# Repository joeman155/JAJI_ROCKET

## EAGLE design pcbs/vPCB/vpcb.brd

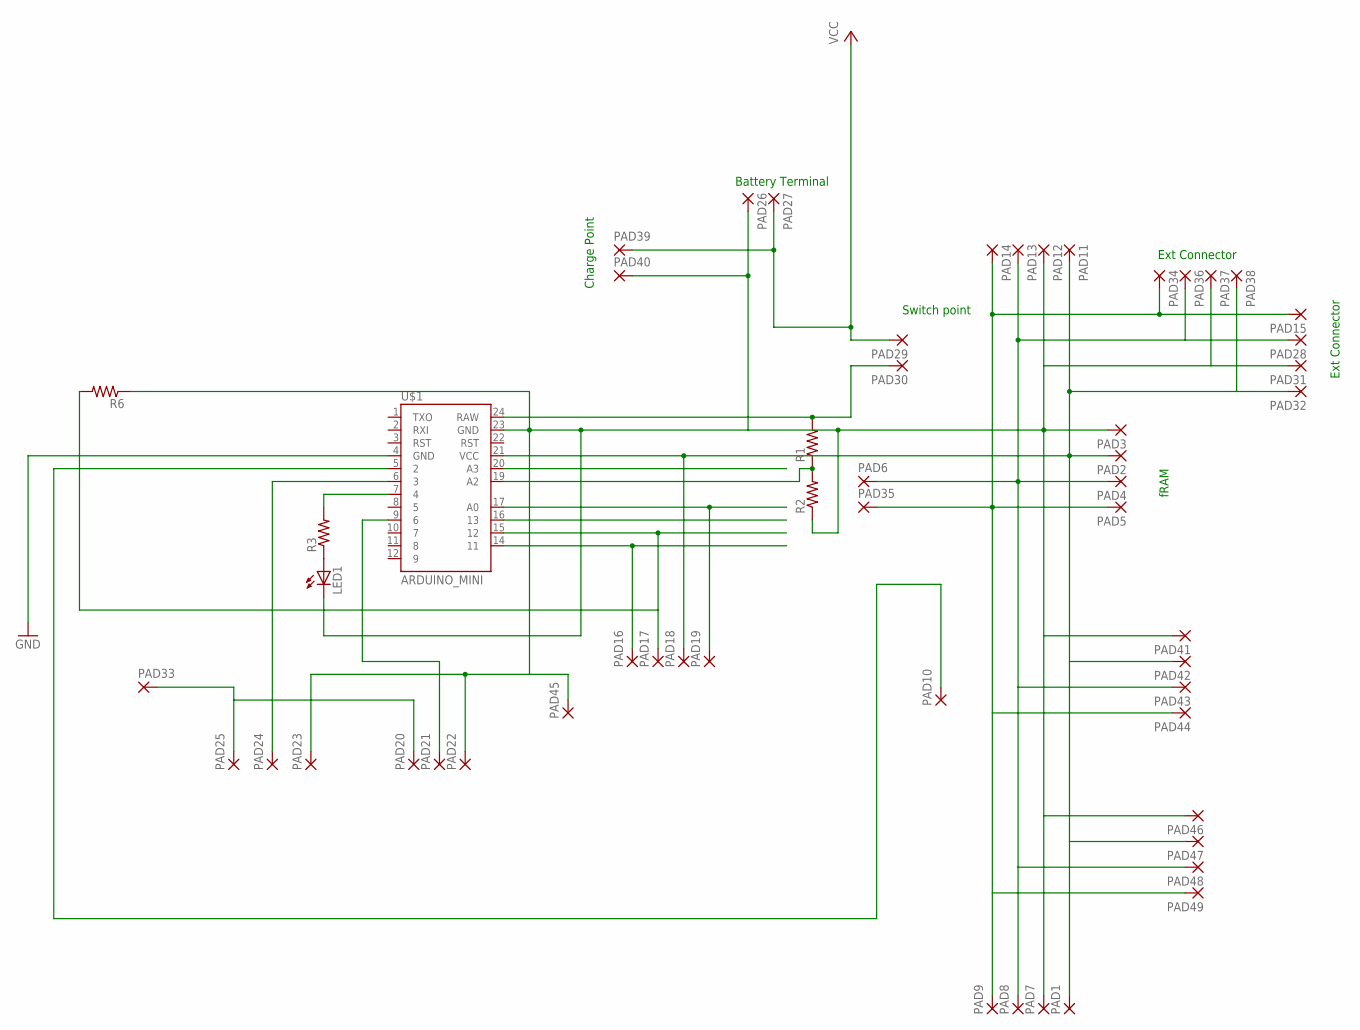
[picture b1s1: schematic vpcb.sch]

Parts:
LED1: LED3MM
PAD1, PAD2, PAD3, PAD4, PAD5, PAD6, PAD7, PAD8, PAD9, PAD10, PAD11, PAD12, PAD13, PAD14, PAD15, PAD16, PAD17, PAD18, PAD19, PAD20, PAD21, PAD22, PAD23, PAD24, PAD25, PAD26, PAD27, PAD28, PAD29, PAD30, PAD31, PAD32, PAD33, PAD34, PAD35, PAD36, PAD37, PAD38, PAD39, PAD40, PAD41, PAD42, PAD43, PAD44, PAD45, PAD46, PAD47, PAD48, PAD49: 2,15/1,0
R1, R2, R3: R-US_0204/7; 0204/7
R6: R-US_0204/5; 0204/5
U$1: ARDUINO_MINI

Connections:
GND: U$1.4 (GND)
unnamed: PAD4.1, PAD6.1, PAD8.1, PAD13.1, PAD28.1, PAD36.1, PAD43.1, PAD48.1
unnamed: PAD5.1, PAD9.1, PAD14.1, PAD15.1, PAD34.1, PAD35.1, PAD44.1, PAD49.1
unnamed: PAD1.1, PAD2.1, PAD11.1, PAD18.1, PAD32.1, PAD38.1, PAD42.1, PAD47.1, U$1.21 (VCC)
unnamed: PAD30.1, R1.2, U$1.24 (RAW)
unnamed: PAD10.1, U$1.5 (2)
unnamed: PAD20.1, PAD25.1, PAD33.1
unnamed: R1.1, R2.2, U$1.19 (A2)
unnamed: LED1.A, R3.1
unnamed: PAD19.1, U$1.17 (A0)
unnamed: R3.2, U$1.7 (4)
unnamed: PAD24.1, U$1.6 (3)
unnamed: PAD21.1, U$1.9 (6)
unnamed: LED1.K (C), PAD3.1, PAD7.1, PAD12.1, PAD22.1, PAD23.1, PAD26.1, PAD31.1, PAD37.1, PAD40.1, PAD41.1, PAD45.1, PAD46.1, R2.1, R6.1, U$1.23 (GND)
unnamed: PAD17.1, R6.2, U$1.15 (12)
unnamed: PAD16.1, U$1.14 (11)
VCC: PAD27.1, PAD29.1, PAD39.1

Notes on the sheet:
Switch point
Charge Point
Ext Connector
fRAM
Battery Terminal

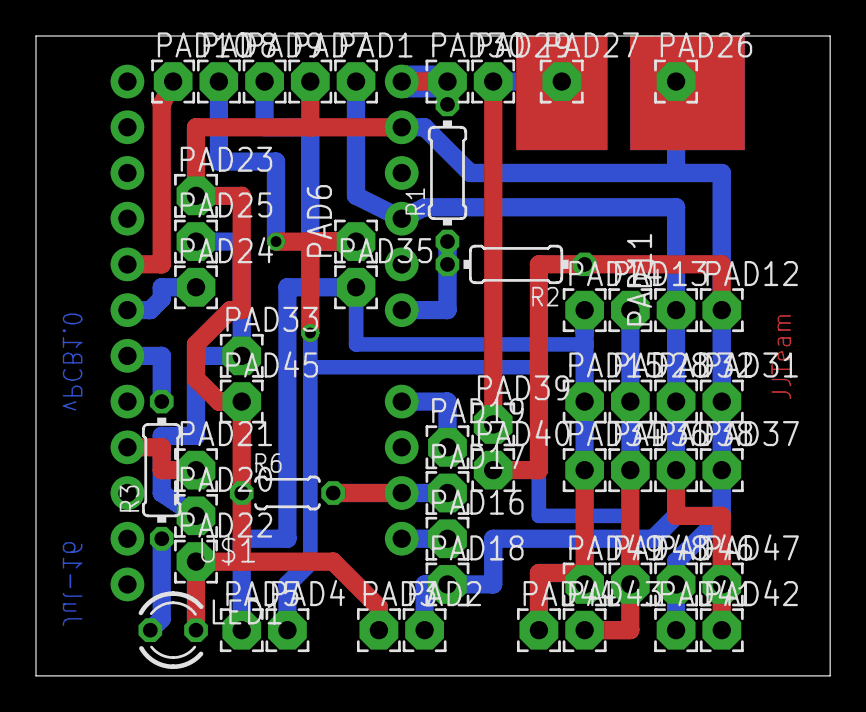
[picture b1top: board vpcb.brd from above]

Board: 2 copper layers, 44.1 x 35.5 mm, 55 parts (0 on the bottom side), 16 nets.

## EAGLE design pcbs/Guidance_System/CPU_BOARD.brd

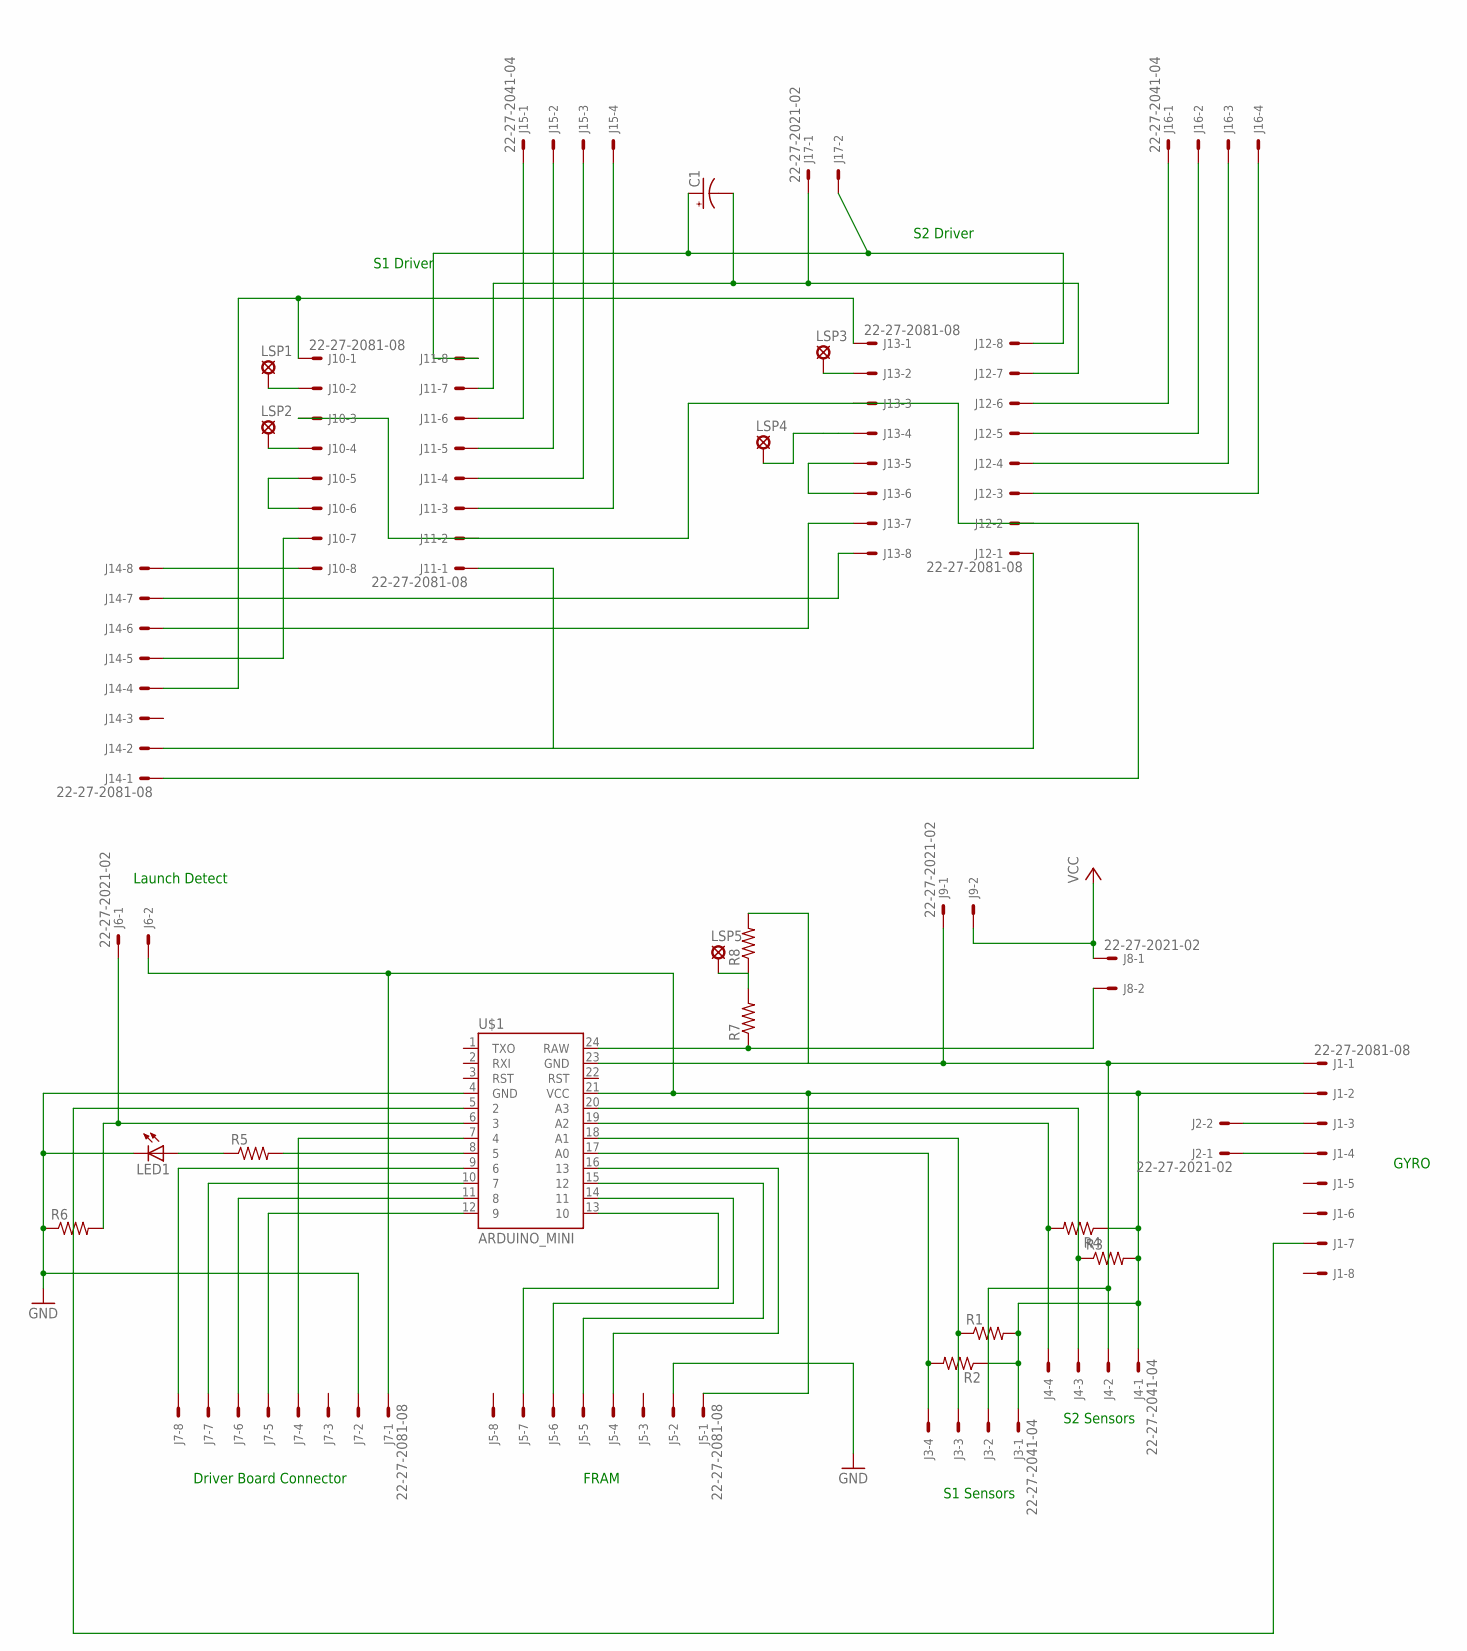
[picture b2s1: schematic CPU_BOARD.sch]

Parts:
C1: CPOL-USE2.5-7; E2,5-7
J1, J5, J7, J10, J11, J12, J13, J14: 22-27-2081-08; 6410-08
J2, J6, J8, J9, J17: 22-27-2021-02; 6410-02
J3, J4, J15, J16: 22-27-2041-04; 6410-04
LED1: LED5MM
LSP1, LSP2, LSP3, LSP4: LSP10
LSP5: LSP11
R1, R2, R3, R4, R5, R6, R7, R8: R-US_0204/5; 0204/5
U$1: ARDUINO_MINI

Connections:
GND: J5.2, J7.2, LED1.K (C), R6.1, U$1.4 (GND)
unnamed: J1.3, J2.2
unnamed: J1.4, J2.1
unnamed: J1.2, J3.1, J4.1, J5.1, J6.2, J7.1, R1.2, R2.1, R3.2, R4.1, U$1.21 (VCC)
unnamed: J10.5, J10.6
unnamed: J8.2, R7.1, U$1.24 (RAW)
unnamed: J1.7, U$1.5 (2)
unnamed: J5.7, U$1.13 (10)
unnamed: J5.6, U$1.14 (11)
unnamed: J4.3, R3.1, U$1.20 (A3)
unnamed: J4.4, R4.2, U$1.19 (A2)
unnamed: J3.3, R1.1, U$1.18 (A1)
unnamed: J3.4, R2.2, U$1.17 (A0)
unnamed: J5.5, U$1.15 (12)
unnamed: J5.4, U$1.16 (13)
unnamed: R5.2, U$1.8 (5)
unnamed: LED1.A, R5.1
unnamed: J6.1, R6.2, U$1.6 (3)
unnamed: J7.8, U$1.9 (6)
unnamed: J13.5, J13.6
unnamed: J7.7, U$1.10 (7)
unnamed: J7.6, U$1.11 (8)
unnamed: J7.5, U$1.12 (9)
unnamed: J7.4, U$1.7 (4)
unnamed: J1.1, J3.2, J4.2, J9.1, R8.2, U$1.23 (GND)
unnamed: J10.4, LSP2.MP
unnamed: J10.8, J14.8
unnamed: J10.7, J14.5
unnamed: J13.7, J14.6
unnamed: J13.8, J14.7
unnamed: J10.2, LSP1.MP
unnamed: C1.+, J11.8, J12.8, J17.2
unnamed: J10.3, J11.2, J12.2, J13.3, J14.1
unnamed: J11.1, J12.1, J14.2
unnamed: C1.-, J11.7, J12.7, J17.1
unnamed: J10.1, J13.1, J14.4
unnamed: J13.4, LSP4.MP
unnamed: J11.6, J15.1
unnamed: J11.5, J15.2
unnamed: J11.4, J15.3
unnamed: J11.3, J15.4
unnamed: J12.6, J16.1
unnamed: J12.5, J16.2
unnamed: J12.4, J16.3
unnamed: J12.3, J16.4
unnamed: J13.2, LSP3.MP
unnamed: LSP5.MP, R7.2, R8.1
VCC: J8.1, J9.2

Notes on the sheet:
FRAM
S1 Sensors
S2 Sensors
GYRO
Launch Detect
Driver Board Connector
S1 Driver
S2 Driver

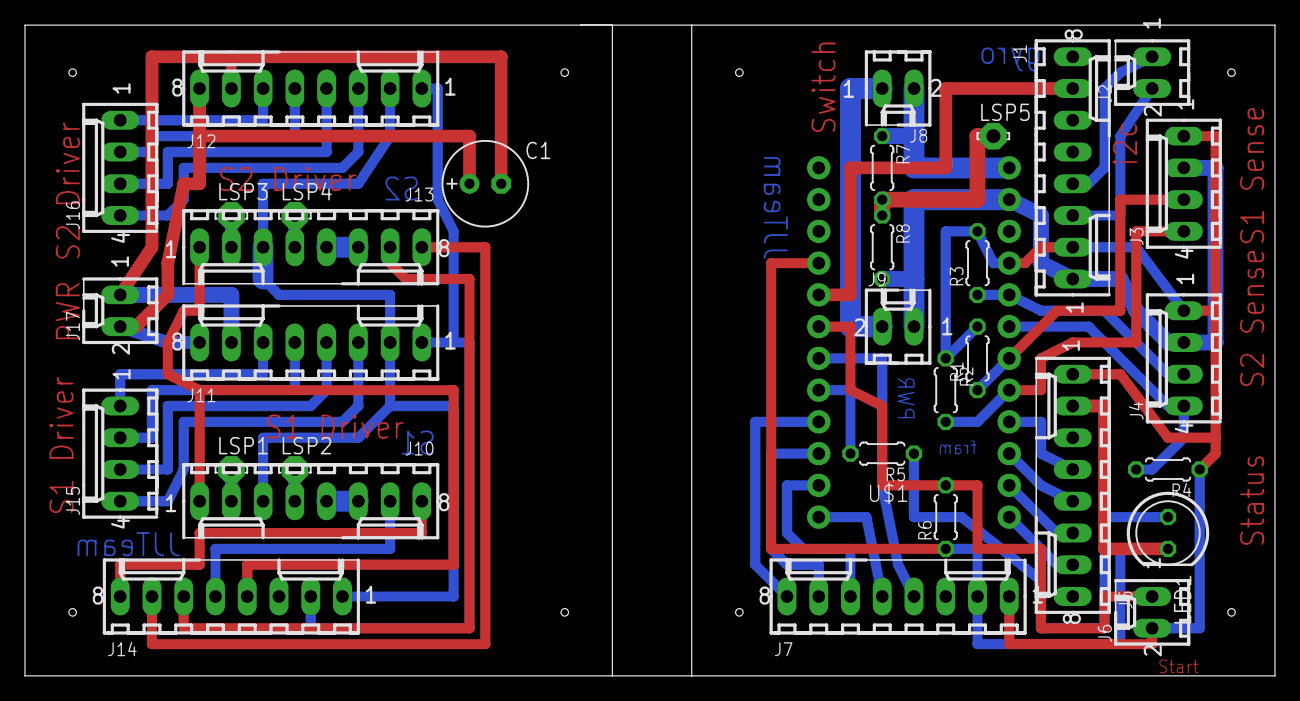
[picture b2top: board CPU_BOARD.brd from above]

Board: 2 copper layers, 100.0 x 52.1 mm, 33 parts (0 on the bottom side), 48 nets.

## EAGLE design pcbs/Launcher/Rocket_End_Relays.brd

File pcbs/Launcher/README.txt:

These files are PCB designs of circuits to launch rockets. These are
shields that will fit on a Freetronics EtherMega

Rocket_End - Signifies PCBS that reside in electronics at end where 
             rocket is.

Operator_End - (No files as of yet)

The second part indicates the main component on them.
- Relays  - Means relays to perform launch sequence 
 [There is also facility for camera and RFD900 module]

- Sensors - A pile of sensors that might be useful
 [Sensors/devices include CopernicusGPS, RTC, IMU, Air pressure measurement]

As you can appreciate for normal launch sequence, only the 'Relays' shield is
required. However, for a Rockoon, at will be advantegous to have a 'Sensors'
shield installed as well to help collect other information (GPS, IMU, 
air pressure, temp, etc)

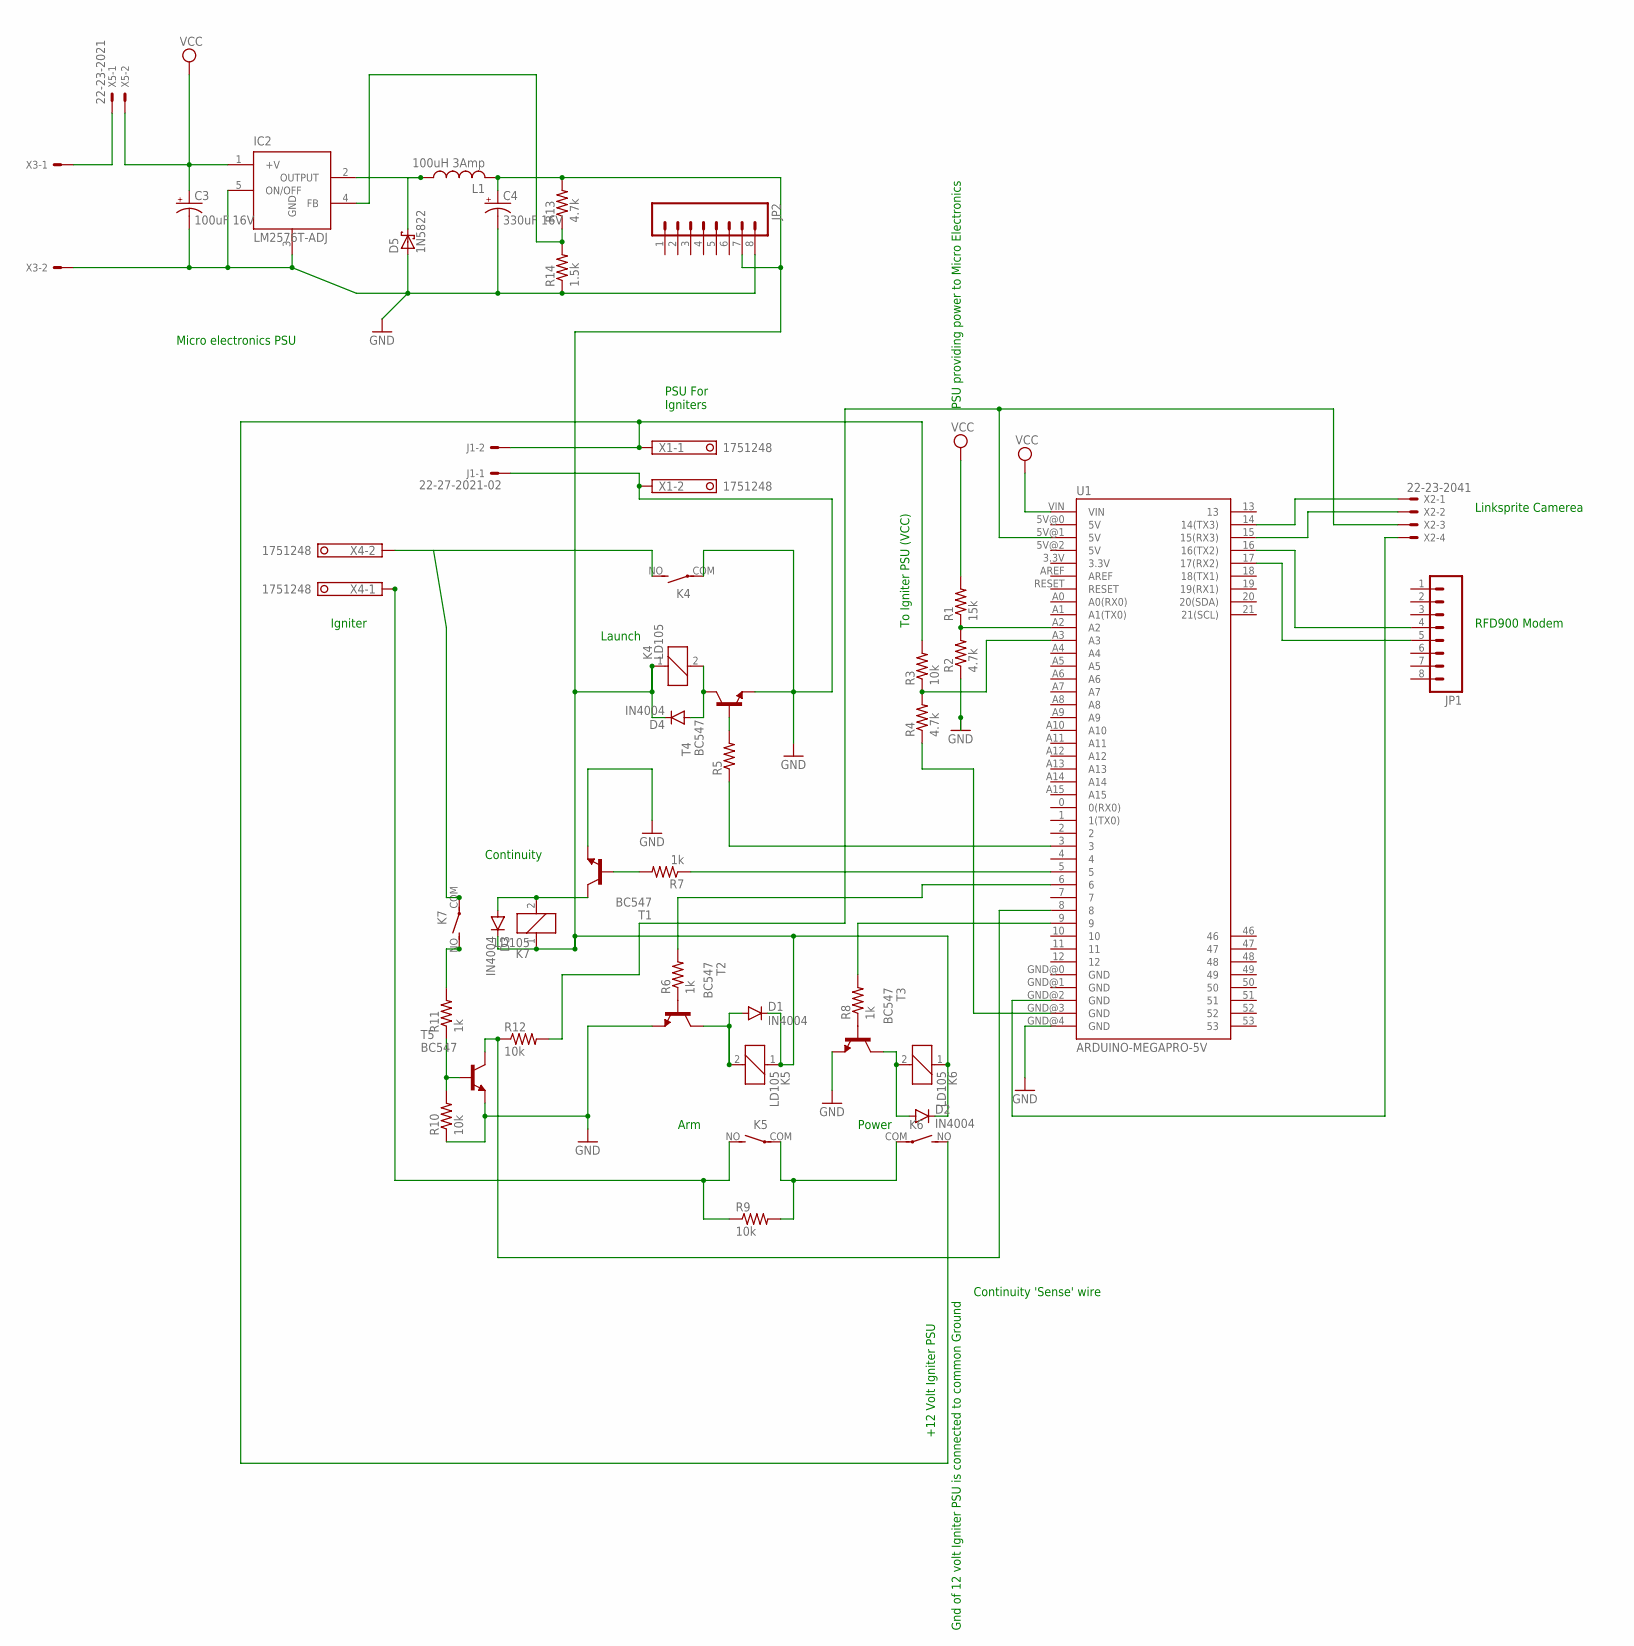
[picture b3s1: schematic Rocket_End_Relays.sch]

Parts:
C3: 100uF 16V; E2-4
C4: 330uF 16V; E2-4
D1, D2, D3, D4: IN4004; DIODE-1N4148
D5: 1N5822; C4111-15
IC2: LM2576T-ADJ; TO220-5
J1: 22-27-2021-02; 6410-02
JP1, JP2: M08; 1X08_ROUND
K4, K5, K6, K7: LD105; LD
L1: 100uH 3Amp; TJ4-U1
R1: 15k; 0204/7
R2, R4: 4.7k; 0204/7
R3, R9, R12: 10k; 0204/7
R5: R-US_0204/7; 0204/7
R6, R7, R8: 1k; 0204/7
R10: 10k; 0207/7
R11: 1k; 0207/12
R13: 4.7k; 0204V
R14: 1.5k; 0207/7
T1, T2, T3, T4, T5: BC547; TO92
U1: ARDUINO-MEGAPRO-5V; ARDUINO_MEGA-PRO-5V
X1, X4: 1751248
X2: 22-23-2041
X3, X5: 22-23-2021

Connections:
unnamed: JP1.4, U1.16 (16(TX2))
unnamed: JP1.5, U1.17 (17(RX2))
unnamed: R3.1, R4.2, U1.A3
unnamed: R7.1, U1.5
unnamed: C4.+, D1.C, D2.C, D3.C, D4.C, JP2.7, K4.1, K5.1, K6.1, K7.1, L1.2, R13.2
unnamed: U1.14 (14(TX3)), X2.1
unnamed: R1.1, R2.2, U1.A2
unnamed: R5.1, U1.3
unnamed: R6.2, U1.6
unnamed: R6.1, T2.2 (B)
unnamed: R8.1, T3.2 (B)
unnamed: R5.2, T4.2 (B)
unnamed: R7.2, T1.2 (B)
unnamed: R8.2, U1.9
unnamed: K4.NO (S), K7.COM, X4.2
unnamed: U1.GND@2 (GND), X2.4
unnamed: K5.NO (S), R9.1, X4.1
unnamed: X3.1, X5.1
unnamed: D4.A, K4.2, T4.3 (C)
unnamed: D3.A, K7.2, T1.3 (C)
unnamed: D2.A, K6.2, T3.3 (C)
unnamed: D1.A, K5.2, T2.3 (C)
unnamed: R12.2, U1.5V@1 (5V), X2.3
unnamed: R4.1, U1.GND@3 (GND)
unnamed: R12.1, T5.3 (C), U1.8
unnamed: U1.15 (15(RX3)), X2.2
unnamed: K5.COM, K6.COM, R9.2
unnamed: J1.2, K6.NO (S), R3.2, X1.1
unnamed: K7.NO (S), R11.2
unnamed: R10.2, R11.1, T5.2 (B)
unnamed: C3.-, C4.-, D5.A, IC2.3 (GND), IC2.5 (ON/OFF), J1.1, JP2.8, K4.COM, R2.1, R10.1, R14.1, T1.1 (E), T2.1 (E), T3.1 (E), T4.1 (E), T5.1 (E), U1.GND@4 (GND), X1.2, X3.2
unnamed: D5.C, IC2.2 (OUTPUT), L1.1
unnamed: IC2.4 (FB), R13.1, R14.2
VCC: C3.+, IC2.1 (+V), R1.2, U1.VIN, X5.2

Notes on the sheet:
Linksprite Camerea
RFD900 Modem
To Igniter PSU (VCC)
Launch
Power
Arm
Continuity
Continuity 'Sense' wire
Igniter
+12 Volt Igniter PSU
Gnd of 12 volt Igniter PSU is connected to common Ground
PSU providing power to Micro Electronics
PSU For Igniters
Micro electronics PSU

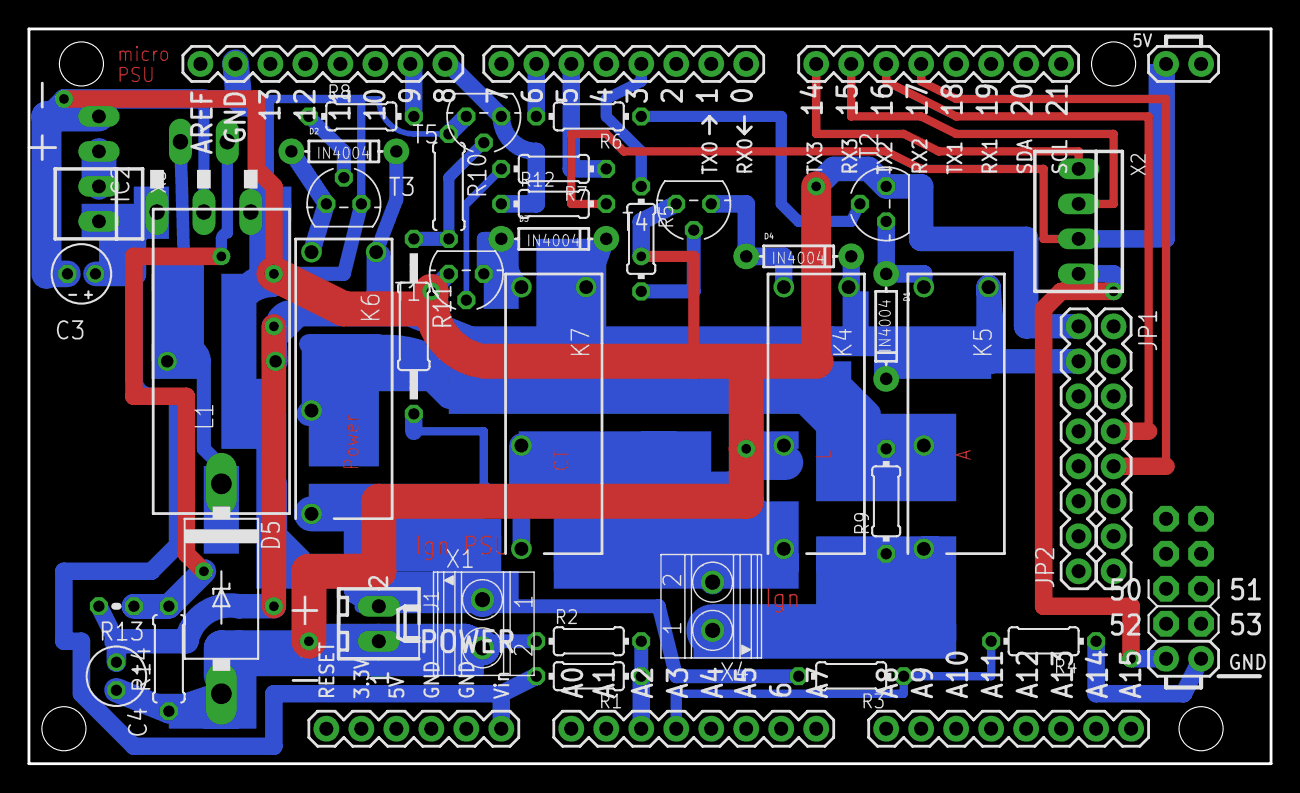
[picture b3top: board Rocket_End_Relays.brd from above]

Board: 2 copper layers, 90.2 x 53.3 mm, 41 parts (1 on the bottom side), 34 nets.

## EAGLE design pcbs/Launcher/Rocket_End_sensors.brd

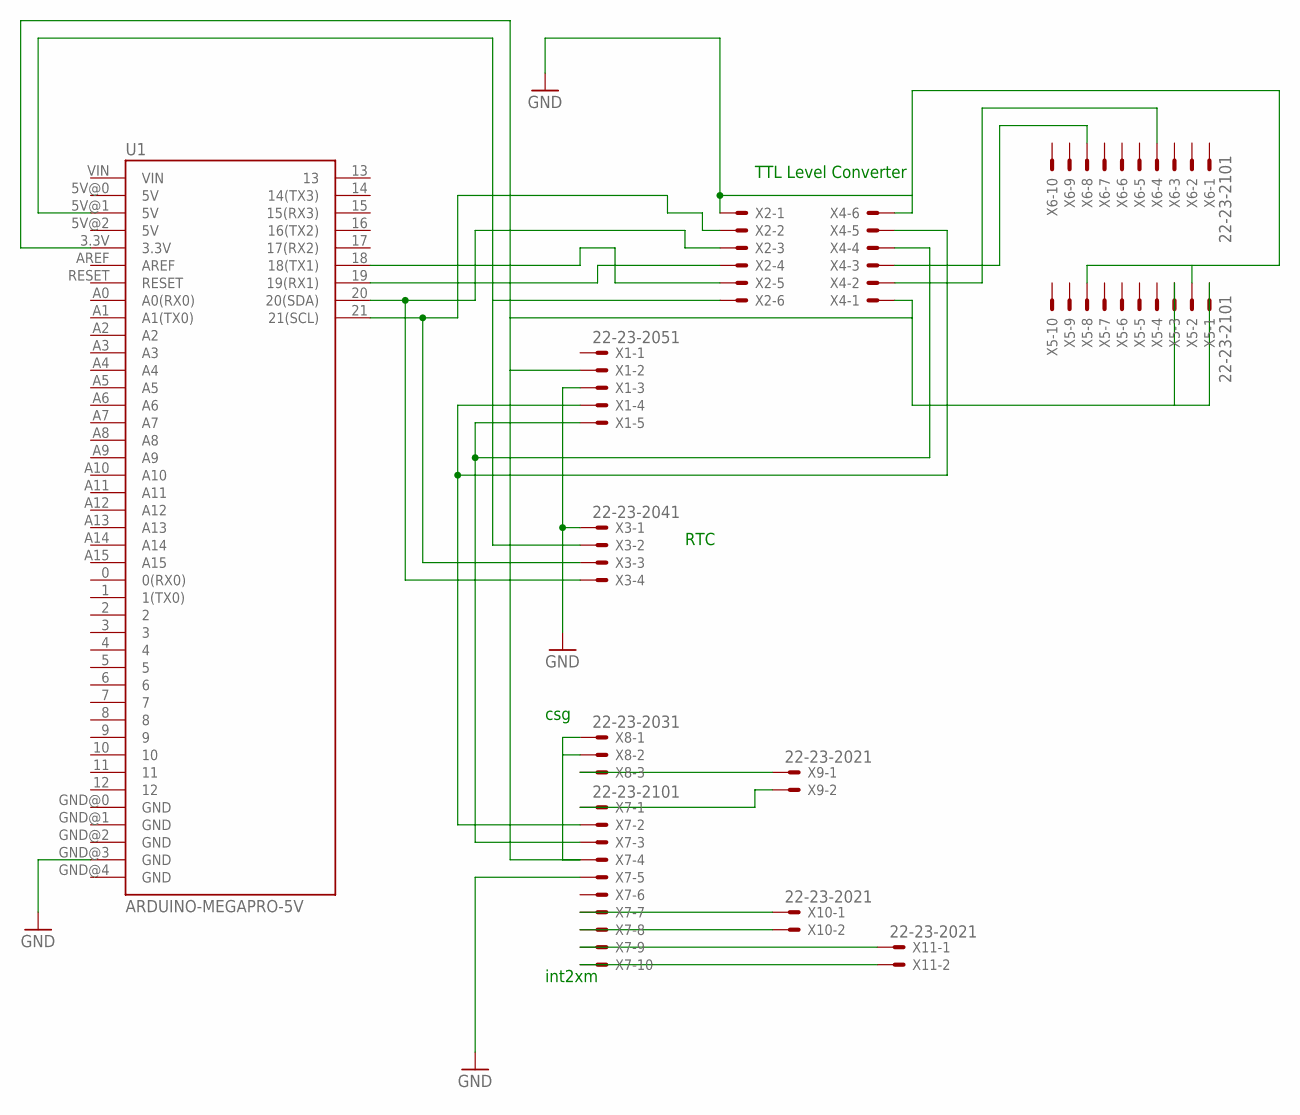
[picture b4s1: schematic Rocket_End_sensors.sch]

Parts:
U1: ARDUINO-MEGAPRO-5V; ARDUINO_MEGA-PRO-5V
X1: 22-23-2051
X2, X4: 22-23-2061
X3: 22-23-2041
X5, X6, X7: 22-23-2101
X8: 22-23-2031
X9, X10, X11: 22-23-2021

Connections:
GND: U1.GND@3 (GND), X1.3, X2.1, X3.1, X4.6, X5.2, X5.8, X7.5
unnamed: U1.19 (19(RX1)), X2.4
unnamed: U1.21 (21(SCL)), X2.2, X3.3
unnamed: U1.18 (18(TX1)), X2.5
unnamed: U1.3.3V, X1.2, X4.1, X5.1, X5.3, X7.4, X8.1, X8.2
unnamed: U1.20 (20(SDA)), X2.3, X3.4
unnamed: X4.3, X6.8
unnamed: X8.3, X9.1
unnamed: X4.2, X6.4
unnamed: X7.1, X9.2
unnamed: X7.7, X10.1
unnamed: X7.8, X10.2
unnamed: X7.9, X11.1
unnamed: X7.10, X11.2
unnamed: X1.5, X4.4, X7.3
unnamed: X1.4, X4.5, X7.2
unnamed: U1.5V@1 (5V), X2.6, X3.2

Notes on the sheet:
RTC
TTL Level Converter
int2xm
csg

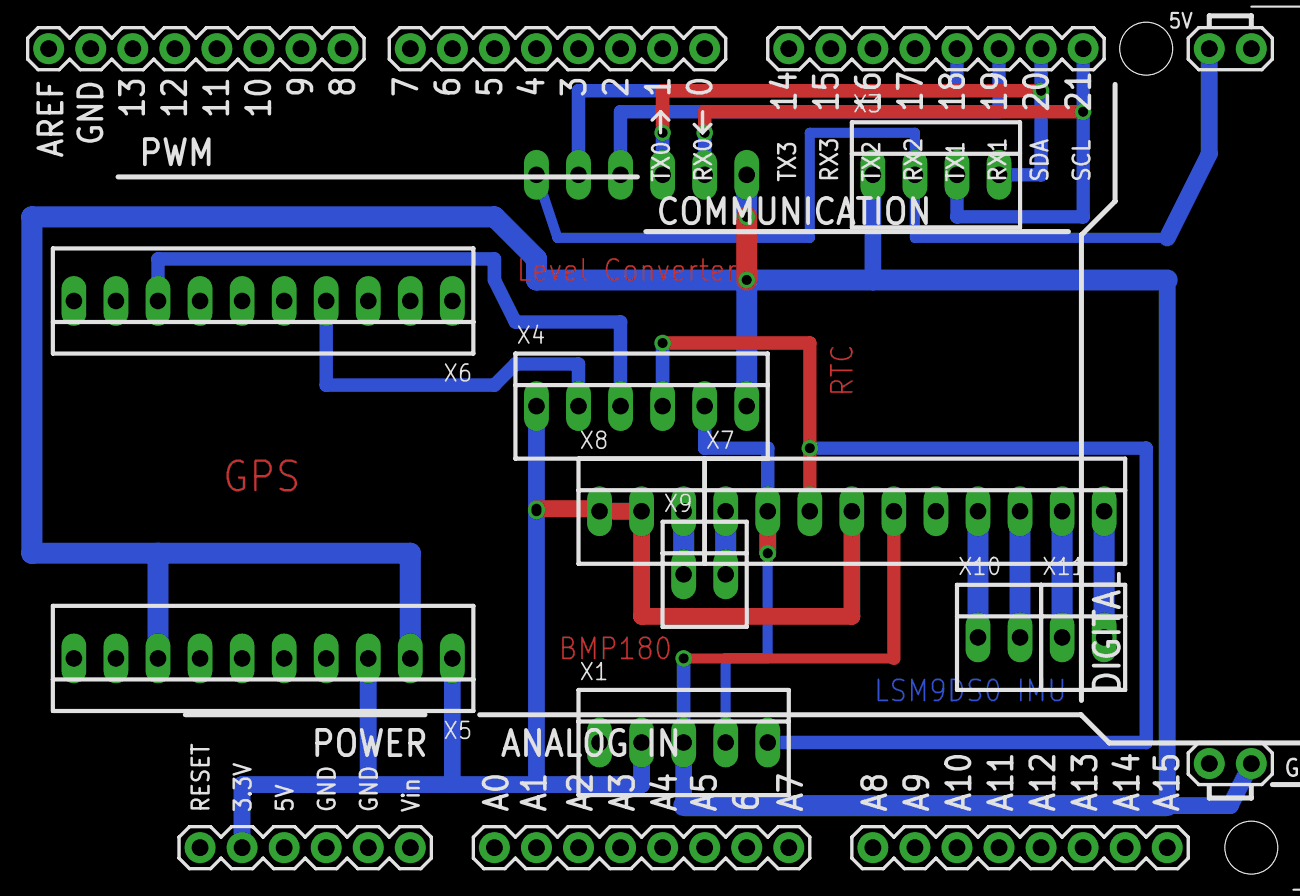
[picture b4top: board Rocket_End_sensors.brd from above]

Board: 2 copper layers, 12 parts (1 on the bottom side), 17 nets.

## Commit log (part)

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2015-07-26 * Add routine to see if pending requests (after latest known status)
2015-07-27 * WOrk on status codeing.
2015-07-27 * Refining way status js is being done.
2015-07-27 * Default photos status
2015-07-28 * Formatting of code * pausing of Hab page added. (reload_paused)
2015-07-28 * Sorted serious issue wit hmore launch_console.php being requested when flipping between pages. restricted to just ONE interval job.
2015-08-03 * Correcting the right-angle connector tracks for a RFD900p module connected logo up. Also made sure it was 10mm from the edge of the pdb * Put in correct 2 pin screw terminal blocks with pitch of 3.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
2015-08-09 * Widened some tracks * Put 2 x 2-pin connector for 7.4 PSU and Switch.
2015-08-10 * Moving across pins, so we don't use pin 4. Pin 4 is used by SDCARD CS.
2015-08-12 * A bit more debugging added.
2015-08-12 * Clarification of pins in comments * Changed Launch Pin to pin 3 * Increased Continuity test delays.
2015-08-16 * Updating web scripts to reflect change in measurements recording.
2015-08-17 * Fixing issue with status page...dbh error.
2015-08-22 * Got Basic IMU working at same time as GPS and RTC.
2015-08-24 * Working on IMU code....commenting out other pieces of code.
2015-08-26 Matix for rotation was incorrect. When rotating around the global Z axis, the computed Z accel changed. It shouldn't have. Put in new matrix.
2015-08-29 * Accepted that Dead Reckoning is not going to work and will implement code so we can atleast monitor its orientation which will still be extremely helpful.
2015-09-03 * More updates.
2015-09-03 * Fix to air pressure measurements.
2015-09-04 * Minor fixes to wording
2015-09-05 * Adding some code to help with Voltage Reader on GroundStation
2015-09-06 * Part way through completing voltage gs code.
2015-09-08 * Reducing some delays * Re-issuing 'M' command if a menu operation is performed. so that further menu requests can be performed.
2015-09-09 * Speed up getting back to menu to do launch and continuity test...by exiting menu after invalidating values * Trying in vain to clear out RX buffers...so that the issue with wrong gotit values is re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
2015-09-09 * Adding in countdown timer.
2015-09-10 * More refinements to tracks, making sure the gaps are sufficiently large.
2015-09-10 * Adding +/- at CPU electronics connector.
2015-09-11 * spacing out some of the components a little * moving the camera serial port connector back one step from edge of PCB.
2015-09-12 * Removed some parts from Joe_Sparkfun-boards.lbf * A bit of a small tidy up on board relays
2015-09-12 More of a tidy up.
2015-09-13 * Added code to save the IMU data
2015-09-13 Making this version - GROUND ROCKET ONLY VERSION....so far only done the Arduino card so far.
2015-09-13 * Fixed up timer to show microseconds and not milliseconds.
2015-09-13 * Fixed issue with table imu_t
2015-09-13 Reducing some of the delays in Continuity tests
2015-09-21 * Starting to add code to show orientation of rocket/Balloon in browser
2015-09-21 * Got some control working now... object orientation pitch/roll translates to x/z axis.
2015-09-22 * Adjustments to IMU code to try and get ready for integrating with new webGL
2015-09-22 * Added altitude to D01. (It was missing)
2015-09-24 * some other pcb edit. (nothing important)
2015-09-27 * Implemented method to read requests over any Serial port. Useful for debugging when not using radio modems.
2015-09-27 * Putting in other Serial port and speed to use * Removing voltage delay * Logging messages to pgsql table now * increasing period between voltage measurements and radio stats gathering.
2015-09-27 * Still referencing sqlite db * Granting additional access required to postgres db objects to www-data user.
2015-09-27 * Enable/disable of GS voltage added * Removed Purge of RX after sending of packets. This removes info being sent back to us from RRLS!!
2015-09-27 * Getting timing to work well. The issue with ack/resp is that if the PERL script is 'behind' in the processing of the serial buffer...it gets confused when trying to process ack/responses.
2015-09-29 * Using Profiles...setting periods in functions
2015-10-02 * Managed to get smooth YAW rotations working. i.e. fixed up transition between E of North and W of North.
2015-10-02 * Making R10 behave as toggle.
2015-10-02 * Clean up a little * Removed unrquired IMU text print out * Adding in additional $v_result check for Profile code.
2015-10-04 * Fixed SQL function in gps 1day php code to work with postgres database.
2015-10-04 * Showing rocket profile setting every 3 seconds.
2015-10-04 * Update to install script to comment out sqlite3 steps.
2015-10-07 * Added ssdv code to allow us to decrypt * Modifications to Groundstation to download ssdv packets to a file.
2015-10-07 Got images of 1024/768 working over camera serial link speed of 57600
2015-10-09 * Fixing up error messages...making sure they agree with the spreadsheet
2015-10-09 * Putting in code to download and generate images.
2015-10-11 Pictures now sending down properly. i.e. it creates a picture Then creates ssdv file Then sends ssdv packets down while doing other transmissions as well.
2015-10-13 * Making groundstation use the file name provided by end tag.
2015-10-13 * Adding variable to track # of packets going through...
2015-10-15 * Photo/no photo taking code added....gives us much more control over RLS activities.
2015-10-21 * Enabling ability to change SSDV packet size easily. Set to 64.
2015-10-28 Fixed up brackets in install script
2015-10-28 * Need to talk to modem at slower speed to get around issues with buffers being maxed out.
2015-10-30 * Improvements to speed of routines printing out info to serial port. It is not a good idea to execute sendPacket multiple times...it is slow....it has to write it's info to the microSD as well. Inst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
2015-11-01 * Much work done on Stats gathering * Added kalman files * Added Statistics library
2015-12-04 * Adding code to simulate spin-up of rocket motor
2016-02-16 * Fixing spelling mistakes and formatting text * Turned off debugging
2016-02-18 * Migrating more code from Java simulation to control smoothers
2016-02-18 * Majority of smoother control logic code migrated. * Starting to implement code to control smoothers (move them around)
2016-02-22 * Implementing thresholds...to par back corrective torque
2016-02-25 * Move some variable initialises into SETUP routine * Added test move_x routine...to facilitate testing..e.g. constant velocity testing * Fixed routines to better calculate c1 * Fixed routines that p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
2016-02-27 * Low level control of stepper motors put in place. Required so we can move them at exactly the same time.
2016-03-04 * Managed to get IMU working - with interrupts.
2016-03-10 * Added more comments on some code...to better explain values and processes * Removing unrequired variables * Moving some variable declarations to top...because they are reused a few times * Includin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
2016-03-11 * Implemented means of disabling FRAM code if FRAM not found * Implemented means of disabling IMU code if we decide to disable it (because we know it isn't present, or don't wish to use it) * Fixed i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
2016-03-13 * Trying different starting angles for S1/S2 * Commented out code to clear out FRAM and 5 second delay to speed up getting it started (Reduce over heating of motor) * Added LED to pin 5 to indicate s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
2016-03-15 * Reduced weight of smoother to what it is - 23grams * Reduced torque_percent to 50% - to reduce slippage * Removed debugging * Fixed routines in smoother_step_3 to better calculate the direction to 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
2016-03-17 * Setting cx_min in setup() and explicity casting as a LONG * Setting Torque_percent to 50% * Correctly casting c0 and cx_min as long when printing out * Short-hand used in showing values (reduce pro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
2016-03-19 * Removing old commented out code * Implementing code to allow microstepping * Added in debugging to giving timings...to see how we are performing.
2016-03-20 * Progressed timings code enough to turn motor 90degrees
2016-03-21 * Getting rid of pulse_firsttime (using i_step == 0) * Stopping re-calc of immediate angle move (if no neutral move done) * Added more timing variables ts1, ts2, ts3. Will move later. * Put in less C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
2016-03-24 * Reverting back to previous settings to reduce step skipping.
2016-03-27 * Disabled debugging * Finished off implementing calibration of Smoothers * Shortening of some text in debugging/info to reduce memory foorprint
2016-03-27 * Removed old and probably unrequired ts* variables * Putting 'in memory of Kate' comment at top of code.
2016-03-29 * Added Driver board. Many corrections and refinements.
2016-04-03 * Made boards a lot smaller a much better layout!
2016-04-05 * Adding Payload Design files to GitHub
2016-04-07 * Re-org'd tracks. Looks tidier
2016-04-07 * Moving sensor connectors a bit further apart.
2016-04-07 * Moved 'start' top level track text to side...so it won't get drilled out.
2016-04-07 * Moved i2c label out of the way. prevent short circuits
2016-04-09 * Added in Lengths file * Updates to payload files to take into account increased size in Tray * Fixed airframe which had holes in wrong spot.
2016-04-11 * Added additional register setting (but ultimately not used) * Additional delay (1 second) while Gyro is started up * Renamed calibrateGyro to calibrate_gryo * Resolved issue with erronous high valu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
2016-04-15 * Created Disc and Phenolic Spacer * Reduced length of airframe back to 310mm (removed space 2 x 2mm in inter-mount) * Added 'centre' crosshairs in drill holes on other drawings to aid in transferrin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
2016-04-25 Opened project file...no actual changes to code
2016-04-27 * Moved rivet holes (that were for the payload bay) 20mm from top, to secure the Nose Cone instead. This is because we can't use Rivets to secure the payload.
2016-05-01 * Updated rivet holes , so we have three instead of four.
2016-05-03 * Added Bulkhead file. * Other minor updates
2016-05-11 * Clean up Camera Payload bottom tray. * Commenting out AdaFruit Code for Air Pressure Sensor * Adding in code to start initializing Air Pressure sensor ourselves, so we can store values to FIFO...in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
2016-05-12 * Coding routine to wait until we have 32 air pressure and temperature measurements * Coded to save these measurements in last 160 bytes of the fRAM * Updating FRAM to extract and display temperature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
2016-07-15 Many refinements to vPCB. - Adding ID, date build - Adding charge point - Adding LED - Adding voltage-test resistors - Fixing battery connector (was around the wrong way) - Adding sufficient space (t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
2016-07-24 * minor updates
2016-07-25 * all pieces in place (prior to creating final joined version, in Payload-joined)
2016-08-05 * Fixing trench issue for PCB. Was too wide. Now back to 1mm * Adding space for wires at top/bottom of PCBs * Increasing width of tabs by 0.25mm, to improve robustness * Adding vertical sections for 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
2016-08-14 * Created design of weight holder
2016-08-21 * Basic functionality works, but freezes. Much more work to do.
2016-09-03 * Working on threshold sensing.
2016-09-16 * Created code to track last ~70 packets, in an effort to ensure when launch begins, we can not overwrite data that was collected a few seconds before the launch event. So we can be sure to get as mu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
2016-09-18 * Added ApplicationMonitor to try and assist in debugging the occasional hangs I experience. * Resolved issue with setting of timer1 after launch has begun, so that the correct delay occurs. I had to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
2016-09-24 * Added PRAGAMA defs to allow removing Air Pressure code from final combined code * Update fram3Addr to be framPtr (which is more generic) .... getting rid of BANK3 reference! * Top servo/bottom serv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
2016-10-04 * Added place for Rotatory switch * Adjusted Testing acceleration threshold to be greater then 1g. So gravity doesn't trigger it off. * Adding in routines to control both servos * Corrected servo pins
2016-10-16 Controller1 ------------- * Disabling DEBUG * Putting Servo initiation/movement AFTER the calibration routines. This ensures no servo vibration that could disrupt calibration and cause an abort * Usi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
    3-D design
    ----------
    * Added in JIG top section to hold payload up for testing (Before putting into air-frame)
2017-01-01 * Got IMU Stats gathering working better...was not showing some var and avg

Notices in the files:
parts and their libraries:
Joe_SparkFun-Boards: Licensing: Creative Commons ShareAlike 4.0 International - https://creativecommons.org/licenses/by-sa/4.0
